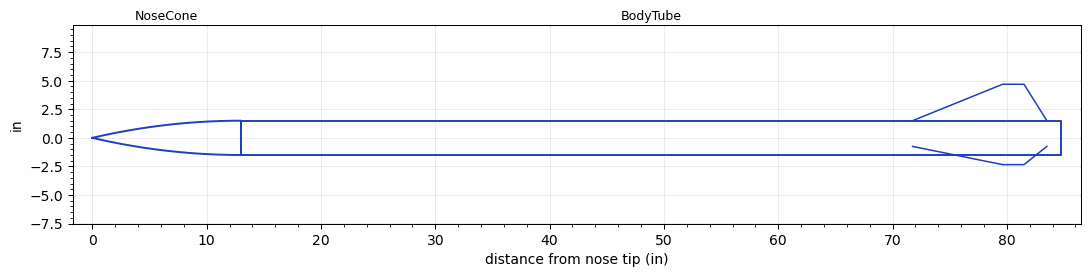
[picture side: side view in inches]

<RASAeroDocument>
 <FileVersion>2</FileVersion>
 <RocketDesign>
  <NoseCone>
   <Length>13</Length>
   <Diameter>3</Diameter>
   <Shape>Tangent Ogive</Shape>
   <Location>0</Location>
  </NoseCone>
  <BodyTube>
   <Length>71.75</Length>
   <Diameter>3</Diameter>
   <RailGuideDiameter>0.375</RailGuideDiameter>
   <RailGuideHeight>0.3438</RailGuideHeight>
   <Location>13</Location>
   <Fin>
    <Count>3</Count>
    <Chord>11.75</Chord>
    <Span>3.1875</Span>
    <SweepDistance>7.875</SweepDistance>
    <TipChord>1.875</TipChord>
    <Thickness>0.25</Thickness>
    <Location>13</Location>
    <AirfoilSection>Square</AirfoilSection>
    <FX1>1.5</FX1>
    <FX3>1.25</FX3>
   </Fin>
  </BodyTube>
  <Surface>Smooth (Zero Roughness)</Surface>
  <ModifiedBarrowman>False</ModifiedBarrowman>
  <Turbulence>False</Turbulence>
  <UseBooster1>False</UseBooster1>
  <UseBooster2>False</UseBooster2>
  <Comments>Gary Byrum
LDRS-26
Jean Dry Lake

Barometric Altimeter
Altitude = 5732 ft

RASAero II Prediction = 5281 ft
Error = -7.87%
</Comments>
 </RocketDesign>
 <LaunchSite>
  <Altitude>2750</Altitude>
  <Pressure>0</Pressure>
  <RodAngle>0</RodAngle>
  <RodLength>10</RodLength>
  <Temperature>100</Temperature>
  <WindSpeed>0</WindSpeed>
 </LaunchSite>
 <Recovery>
  <Altitude1>1000</Altitude1>
  <Altitude2>1000</Altitude2>
  <DeviceType1>None</DeviceType1>
  <DeviceType2>None</DeviceType2>
  <Event1>False</Event1>
  <Event2>False</Event2>
  <Size1>1</Size1>
  <Size2>1</Size2>
  <EventType1>None</EventType1>
  <EventType2>None</EventType2>
  <CD1>1.33</CD1>
  <CD2>1.33</CD2>
 </Recovery>
 <SimulationList>
  <Simulation>
   <SustainerEngine>J570W  (AT)</SustainerEngine>
   <SustainerLaunchWt>7.75</SustainerLaunchWt>
   <SustainerCG>56</SustainerCG>
   <SustainerIgnitionDelay>0</SustainerIgnitionDelay>
   <Booster1SeparationDelay>0</Booster1SeparationDelay>
   <Booster1IgnitionDelay>0</Booster1IgnitionDelay>
   <IncludeBooster1>False</IncludeBooster1>
   <Booster2Delay>0</Booster2Delay>
   <IncludeBooster2>False</IncludeBooster2>
   <TimetoApogee>15.99027</TimetoApogee>
   <MaxAltitude>5281.163</MaxAltitude>
   <MaxVelocity>834.6983</MaxVelocity>
  </Simulation>
 </SimulationList>
</RASAeroDocument>
